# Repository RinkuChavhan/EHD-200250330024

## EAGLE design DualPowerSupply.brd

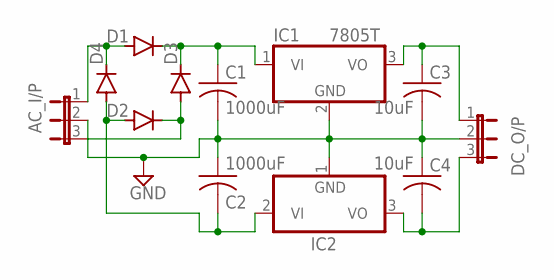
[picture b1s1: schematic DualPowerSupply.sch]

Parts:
AC_I/P: JP2E; JP2
C1, C2: 1000uF; C025_050-025X075
C3, C4: 10uF; C025_050-025X075
D1, D2, D3, D4: 1N4004; DO41-10
DC_O/P: JP2E; JP2
IC1: 7805T; TO220H
IC2: 7905T; TO220H

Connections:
GND: AC_I/P.2, C1.2, C2.1, C3.2, C4.1, DC_O/P.2, IC1.2 (GND), IC2.1 (GND)
unnamed: C2.2, D2.A, D4.A, IC2.2 (VI)
unnamed: AC_I/P.3, D2.C, D3.A
unnamed: C1.1, D1.C, D3.C, IC1.1 (VI)
unnamed: AC_I/P.1, D1.A, D4.C
unnamed: C3.1, DC_O/P.1, IC1.3 (VO)
unnamed: C4.2, DC_O/P.3, IC2.3 (VO)

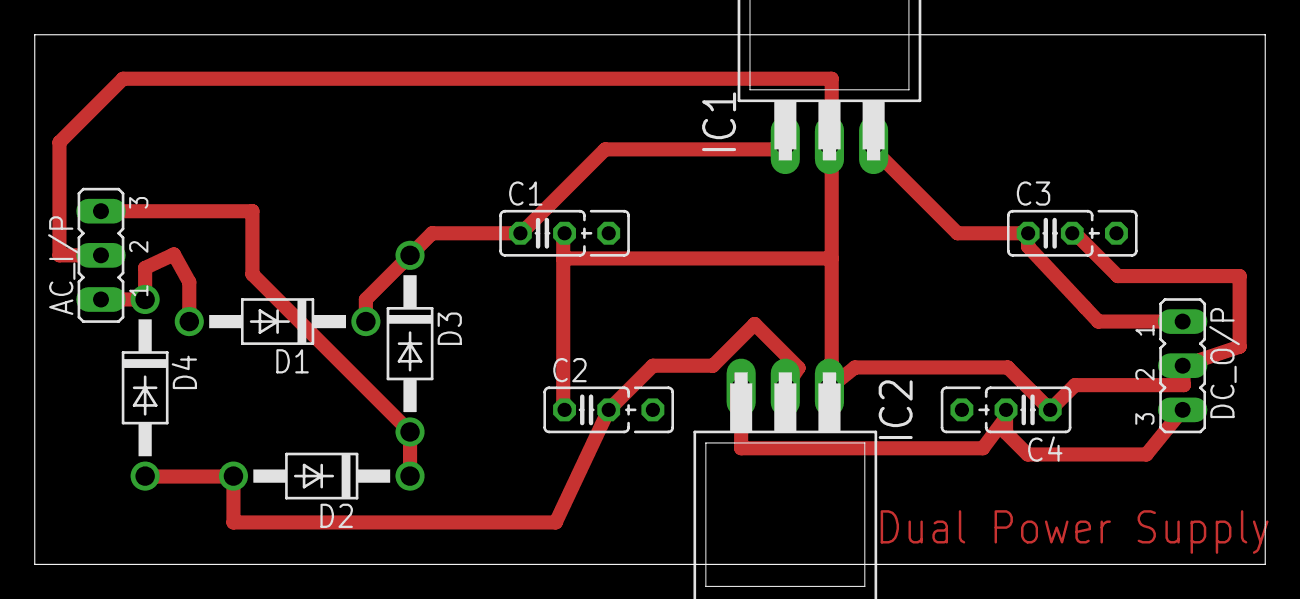
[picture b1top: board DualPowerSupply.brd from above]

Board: 2 copper layers, 70.8 x 30.5 mm, 12 parts (0 on the bottom side), 7 nets.

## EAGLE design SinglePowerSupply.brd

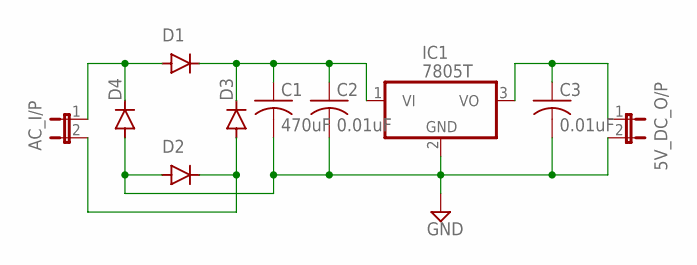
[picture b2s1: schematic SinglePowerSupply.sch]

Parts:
5V_DC_O/P: JP1E; JP1
AC_I/P: JP1E; JP1
C1: 470uF; C025_050-025X075
C2, C3: 0.01uF; C025_050-025X075
D1, D2, D3, D4: 1N4004; DO41-10
IC1: 7805T; TO220H

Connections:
GND: 5V_DC_O/P.2, C1.2, C2.2, C3.2, D2.A, D4.A, IC1.2 (GND)
unnamed: AC_I/P.1, D1.A, D4.C
unnamed: C1.1, C2.1, D1.C, D3.C, IC1.1 (VI)
unnamed: AC_I/P.2, D2.C, D3.A
unnamed: 5V_DC_O/P.1, C3.1, IC1.3 (VO)

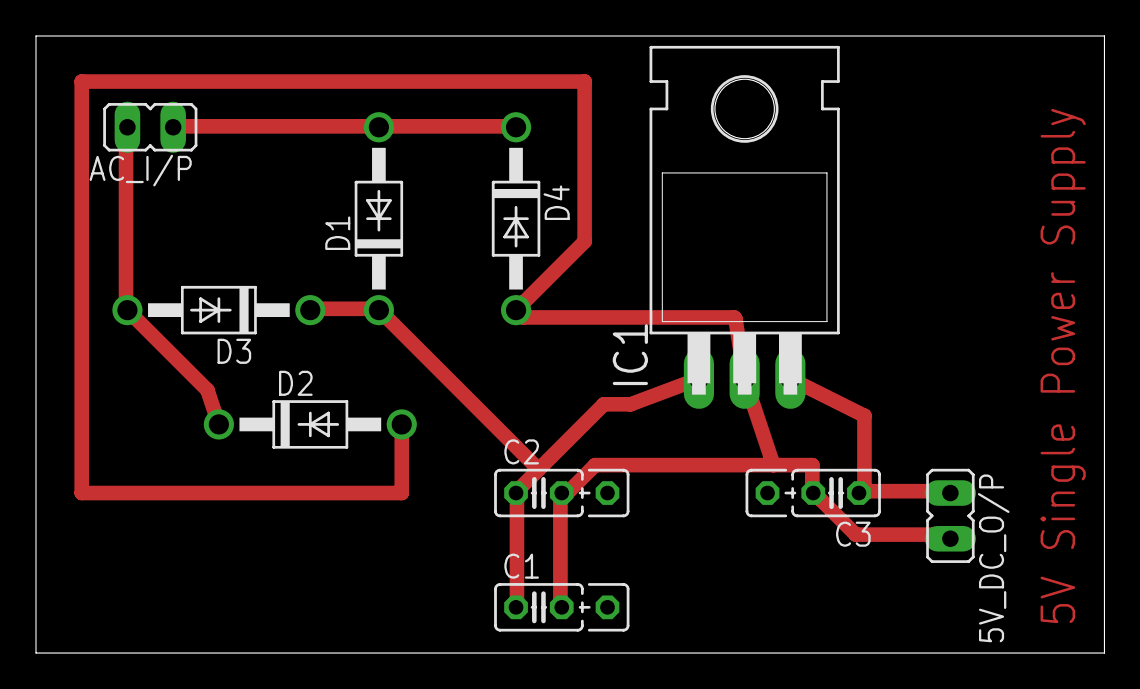
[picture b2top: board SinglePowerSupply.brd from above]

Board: 2 copper layers, 59.4 x 34.3 mm, 10 parts (0 on the bottom side), 5 nets.
